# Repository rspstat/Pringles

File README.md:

# Pringles
- 2025-2 산학프로젝트

<br/>

## 👤 Members
- 프로덕트 오너(Product Owner) : 박세민
- 스크럼 마스터(Scrum Master) : 김규현
- TI 매니저(TI Manager) : 김주훈

<br/>

## 🛠️ Tech Stack

### Frontend
- React `19.2.0`
- Node.js `v22.20.0`
- npm `10.9.3`

### Backend
- Python `3.12.11`
- FastAPI `0.118.1`

<br/>

## 🔗 Link
- [notion](https://www.notion.so/Technical-Definition-Analysis-27183d64f09980dba4ccfc1c0c1e9a1a?source=copy_link)

<br/>

## Activation(백/프론트 각각 그대로 터미널에 복붙, sanhark/ 에서 실행)
back:
```
cd backend
py -3 -m venv .venv
.venv\Scripts\activate
pip install -r requirements.txt
uvicorn app.main:app --reload --port 8000
```

front:
```
cd frontend
npm install
npm run dev
```

<br/>

## Github Push (그대로 bash에 복붙)
```
cd C:\Users\win11\Desktop\assignment\Pringles

# Git 초기화
rm -rf .git
rm -f .gitattributes
git init
git branch -M main
git lfs install

# LFS 추적 설정
git lfs track "**/*.zip"
git lfs track "**/*.rar"
git lfs track "**/*.pdf"
git lfs track "**/*.psd"
git lfs track "**/*.mp4"
git lfs track "**/*.exe"
git lfs track "uploads/**"
git add .gitattributes
git commit -m "chore: LFS 설정"

# .gitignore
cat > .gitignore << EOL
node_modules/
.venv/
venv/
__pycache__/
*.pyc
.env
.DS_Store
EOL

# 전체 커밋
git add .
git commit -m "initial commit: 전체 프로젝트"

# 푸시
git remote add origin https://github.com/rspstat/Pringles.git
git lfs push origin main --all
git push -u origin main --force
```

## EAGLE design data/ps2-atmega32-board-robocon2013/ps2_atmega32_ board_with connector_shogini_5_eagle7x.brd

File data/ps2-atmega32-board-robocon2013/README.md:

View this project on [CADLAB.io](https://cadlab.io/project/1365). 

An interface board between Atmega32 and Sony PS2 controller.

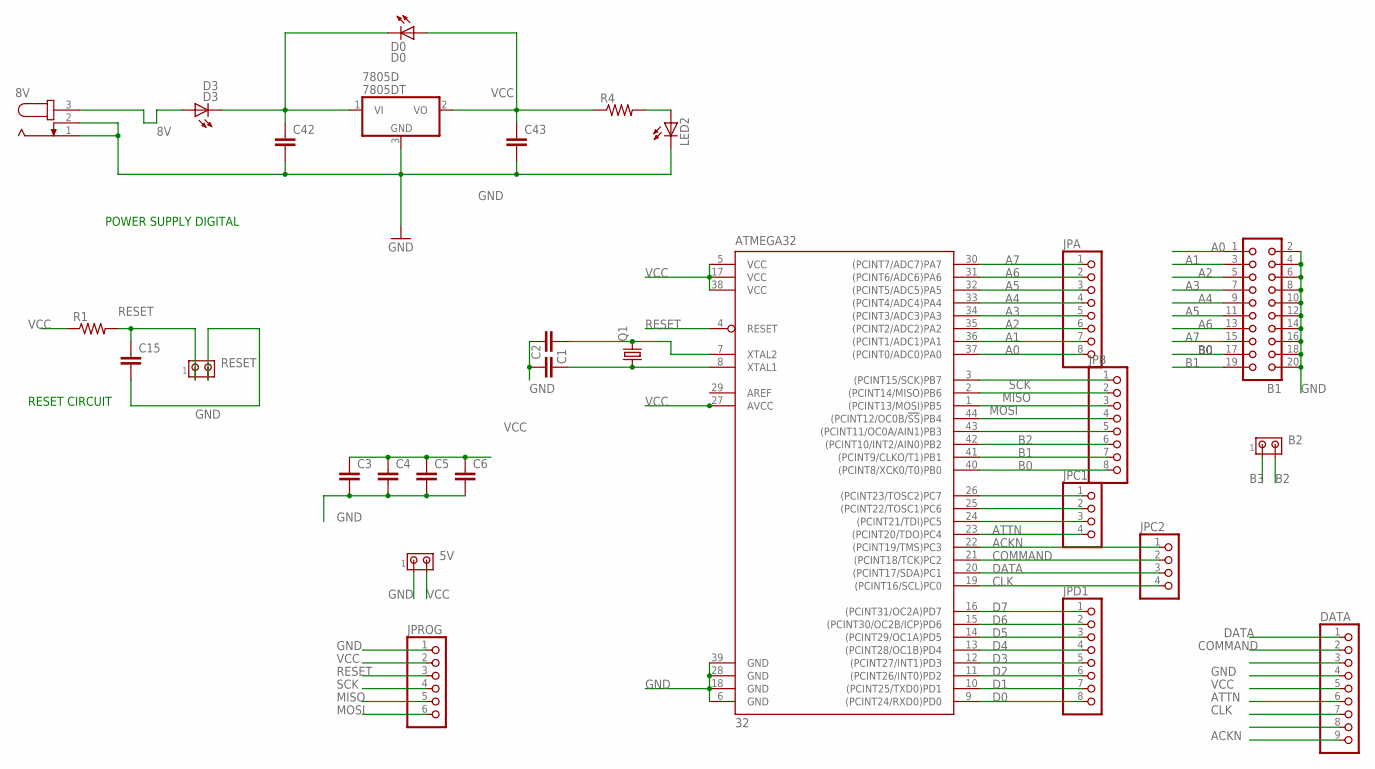
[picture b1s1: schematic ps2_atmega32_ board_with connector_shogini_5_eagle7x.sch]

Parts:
5V: MTA02-100; 10X02MTA
8V: JACK-PLUG0; SPC4077
7805D: 7805DT; TO252
ATMEGA32: 32; TQFP44
B1: CON20L
B2: MTA02-100; 10X02MTA
C1, C2, C3, C4, C5, C6: C-EUC0603K; C0603K
C15, C42, C43: C-EUC0603; C0603
D0: D0; CHIPLED_1206
D3: D3; CHIPLED_1206
DATA: PINHD-1X9; 1X09
JPA: PINHD-1X8; 1X08
JPB: PINHD-1X8; 1X08
JPC1, JPC2: PINHD-1X4; 1X04
JPD1: PINHD-1X8; 1X08
JPROG: PINHD-1X6; 1X06
LED2: LEDCHIPLED_1206; CHIPLED_1206
Q1: CRYSTALHC49S; HC49/S
R1, R4: R-US_R0603; R0603
RESET: MTA02-100; 10X02MTA

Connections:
8V: 8V.3, D3.A
A0: ATMEGA32.37 ((PCINT0/ADC0)PA0), B1.1, JPA.8
A1: ATMEGA32.36 ((PCINT1/ADC1)PA1), B1.3, JPA.7
A2: ATMEGA32.35 ((PCINT2/ADC2)PA2), B1.5, JPA.6
A3: ATMEGA32.34 ((PCINT3/ADC3)PA3), B1.7, JPA.5
A4: ATMEGA32.33 ((PCINT4/ADC4)PA4), B1.9, JPA.4
A5: ATMEGA32.32 ((PCINT5/ADC5)PA5), B1.11, JPA.3
A6: ATMEGA32.31 ((PCINT6/ADC6)PA6), B1.13, JPA.2
A7: ATMEGA32.30 ((PCINT7/ADC7)PA7), B1.15, JPA.1
ACKN: ATMEGA32.22 ((PCINT19/TMS)PC3), DATA.9, JPC2.1
ATTN: ATMEGA32.23 ((PCINT20/TDO)PC4), DATA.6, JPC1.4
B0: ATMEGA32.40 ((PCINT8/XCK0/T0)PB0), B1.17, JPB.8
B1: ATMEGA32.41 ((PCINT9/CLKO/T1)PB1), B1.19, JPB.7
B2: ATMEGA32.42 ((PCINT10/INT2/AIN0)PB2), B2.2, JPB.6
B3: ATMEGA32.43 ((PCINT11/OC0A/AIN1)PB3), B2.1, JPB.5
CLK: ATMEGA32.19 ((PCINT16/SCL)PC0), DATA.7, JPC2.4
COMMAND: ATMEGA32.21 ((PCINT18/TCK)PC2), DATA.2, JPC2.2
D0: ATMEGA32.9 ((PCINT24/RXD0)PD0), JPD1.8
D1: ATMEGA32.10 ((PCINT25/TXD0)PD1), JPD1.7
D2: ATMEGA32.11 ((PCINT26/INT0)PD2), JPD1.6
D3: ATMEGA32.12 ((PCINT27/INT1)PD3), JPD1.5
D4: ATMEGA32.13 ((PCINT28/OC1B)PD4), JPD1.4
D5: ATMEGA32.14 ((PCINT29/OC1A)PD5), JPD1.3
D6: ATMEGA32.15 ((PCINT30/OC2B/ICP)PD6), JPD1.2
D7: ATMEGA32.16 ((PCINT31/OC2A)PD7), JPD1.1
DATA: ATMEGA32.20 ((PCINT17/SDA)PC1), DATA.1, JPC2.3
GND: 5V.1, 8V.1, 8V.2, 7805D.3 (GND), ATMEGA32.6 (GND), ATMEGA32.18 (GND), ATMEGA32.28 (GND), ATMEGA32.39 (GND), B1.2, B1.4, B1.6, B1.8, B1.10, B1.12, B1.14, B1.16, B1.18, B1.20, C1.2, C2.1, C3.2, C4.2, C5.2, C6.2, C15.2, C42.2, C43.2, DATA.4, JPROG.1, LED2.C, RESET.2
MISO: ATMEGA32.2 ((PCINT14/MISO)PB6), JPB.2, JPROG.5
MOSI: ATMEGA32.1 ((PCINT13/MOSI)PB5), JPB.3, JPROG.6
unnamed: ATMEGA32.7 (XTAL2), C1.1, Q1.2
unnamed: ATMEGA32.8 (XTAL1), C2.2, Q1.1
unnamed: LED2.A, R4.2
unnamed: ATMEGA32.44 ((PCINT12/OC0B/!SS!)PB4), JPB.4
unnamed: ATMEGA32.26 ((PCINT23/TOSC2)PC7), JPC1.1
unnamed: ATMEGA32.25 ((PCINT22/TOSC1)PC6), JPC1.2
unnamed: ATMEGA32.24 ((PCINT21/TDI)PC5), JPC1.3
RESET: ATMEGA32.4 (RESET), C15.1, JPROG.3, R1.2, RESET.1
SCK: ATMEGA32.3 ((PCINT15/SCK)PB7), JPB.1, JPROG.4
VCC: 5V.2, 7805D.2 (VO), ATMEGA32.5 (VCC), ATMEGA32.17 (VCC), ATMEGA32.27 (AVCC), ATMEGA32.38 (VCC), C3.1, C4.1, C5.1, C6.1, C43.1, D0.A, DATA.5, JPROG.2, R1.1, R4.1
VI(5D): 7805D.1 (VI), C42.1, D0.C, D3.C

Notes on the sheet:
RESET CIRCUIT
POWER SUPPLY DIGITAL

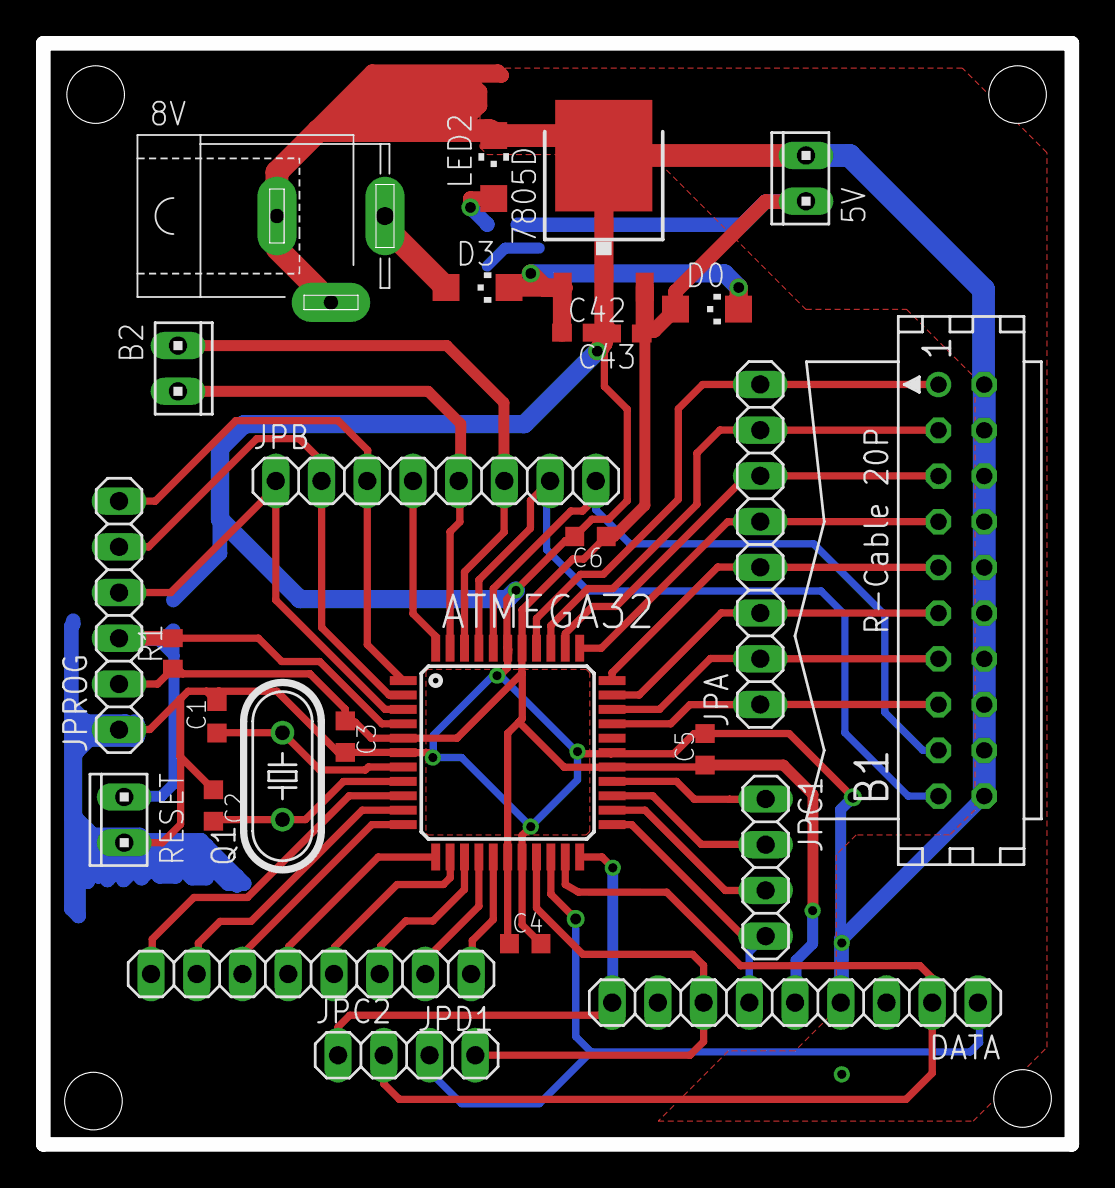
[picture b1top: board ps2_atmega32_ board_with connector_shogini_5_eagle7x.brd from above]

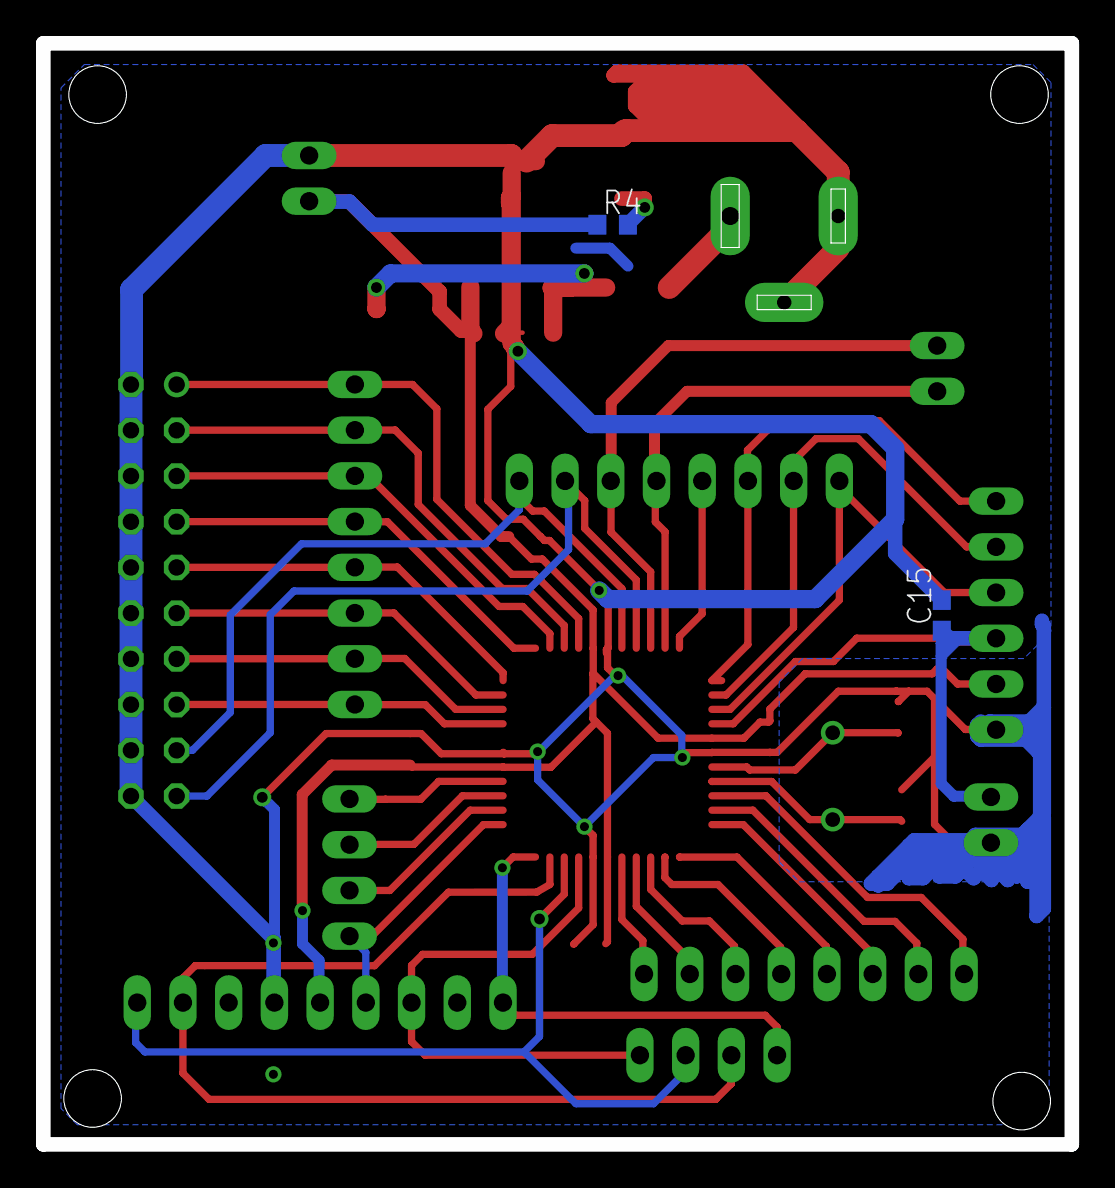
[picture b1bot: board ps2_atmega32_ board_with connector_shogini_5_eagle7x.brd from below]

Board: 2 copper layers, 57.1 x 61.2 mm, 29 parts (2 on the bottom side), 40 nets.

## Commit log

2025-10-08 2025-10-08
2025-11-05 Add Gemini API Key
